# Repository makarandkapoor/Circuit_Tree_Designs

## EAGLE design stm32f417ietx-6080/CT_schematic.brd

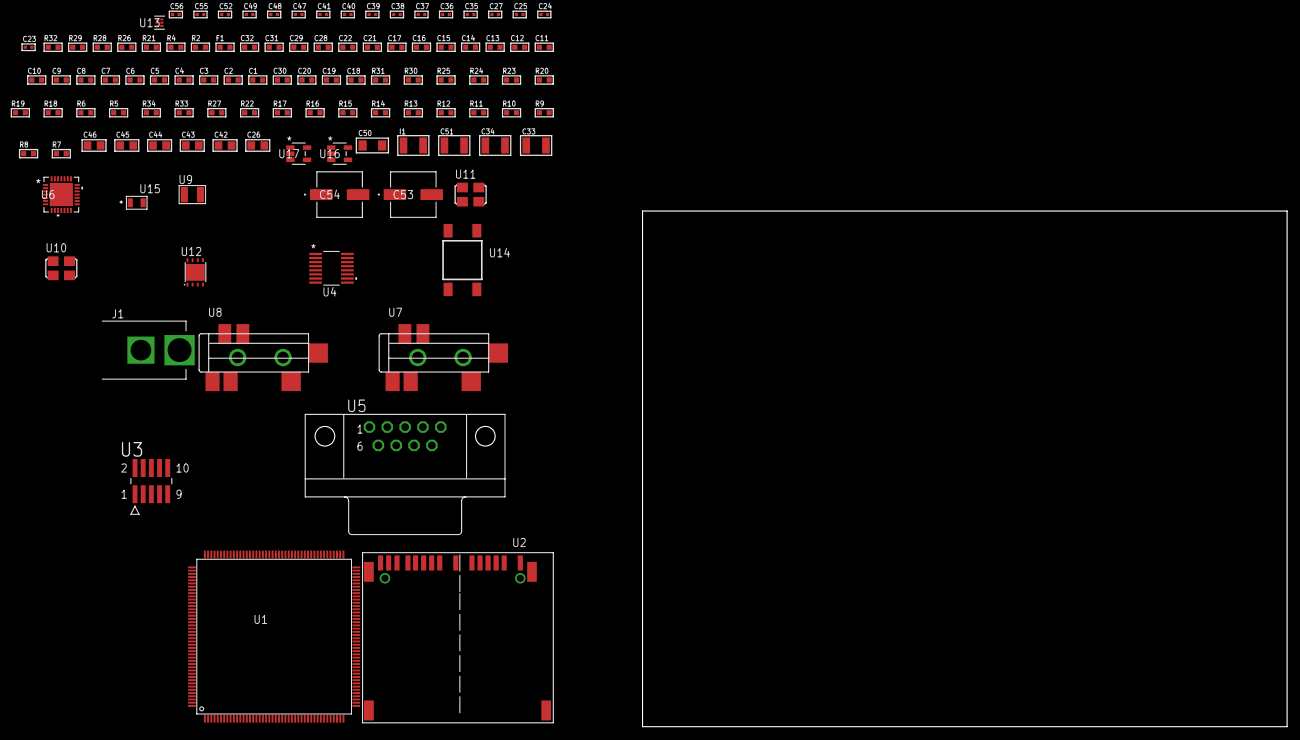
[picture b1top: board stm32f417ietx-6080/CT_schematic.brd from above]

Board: 2 copper layers, 100.0 x 80.0 mm, 108 parts (0 on the bottom side), 57 nets, no tracks yet.

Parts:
C1, C22, C28, C29, C31, C32: 1e-06; C0603
C2, C3, C4, C5, C6, C7, C8, C9, C10, C11, C12, C13, C14, C15, C16, C17: 1e-07; C0603
C18: 4.7e-06; C0603
C19, C20: 2.2e-06; C0603
C21: 1e-08; C0603
C23, C24: 1e-11; C0402
C25, C27, C37, C38, C39, C40, C41, C52: 1e-07; C0402
C26, C42, C43, C44, C45, C46: 1e-05; C0805
C30: 2.2e-07; C0603
C33, C34: 2.2e-05; C1210
C35, C36: 1e-09; C0402
C47, C48, C49, C55, C56: 1e-08; C0402
C50: 1e-05; C1206
C51: 1e-05; C1210
C53, C54: 0.0001; EXV-9H
F1: 240.0; L0603
I1: 1e-05; L1210
J1: PJ-037B; PJ-037B_PACKAGE
R2, R29: 1000.0; R0603
R4: 4700.0; R0603
R5, R6, R18, R19, R20, R30, R31: 10000.0; R0603
R7, R8, R9, R10, R11, R12, R13, R14, R15, R16, R17, R22, R27: 100000.0; R0603
R21: 5.0; R0603
R23, R24, R25: 47000.0; R0603
R26: 680.0; R0603
R28: 2231.0; R0603
R32: 9100.0; R0603
R33: 680000.0; R0603
R34: 120000.0; R0603
U1: STM32F417IET6; LQFP176
U2: 10100565
U3: FTSH-105-01-L-DV-K; SAMTEC_FTSH-105-01-L-DV-K
U4: LTC2804CGN-1#PBF; SSOP-16
U5: 182-009-113R531; 182-009-MALE
U6: WM8731CLSEFL; QFN-28
U7, U8: SJ-43515TS-SMT-TR
U9: ABS07-32.768KHZ-7-T
U10: ASFL1-12.288MHZ-EC-T; ASFL1
U11: ASFL1-25MHZ-NCS; ASFL1
U12: LP3878SDX-ADJ/NOPB; WSON-8
U13: TPS3895ADRYR; SON-6
U14: 4-1437565-2; SW_4-1437565-2
U15: Q65110A2395; LGM67K-G1J2-24-Z
U16, U17: nc7sz125m5x; NC7SZ125M5X

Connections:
CLK_CRYSTAL_U1_9: C23.1, U1.9, U9.1
CLK_CRYSTAL_U1_10: C24.1, U1.10, U9.2
CLK_U1_29: U1.29, U11.3
CLK_U6_1: U6.1, U10.3
GND: C1.2, C2.2, C3.2, C4.2, C5.2, C6.2, C7.2, C8.2, C9.2, C10.2, C11.2, C12.2, C13.2, C14.2, C15.2, C16.2, C17.2, C18.2, C19.2, C20.2, C21.2, C22.2, C23.2, C24.2, C25.2, C26.2, C27.2, C28.2, C29.2, C31.2, C32.2, C36.2, C37.2, C38.2, C39.2, C40.2, C41.2, C42.2, C43.2, C44.2, C45.2, C46.2, C47.2, C48.2, C49.2, C50.2, C51.2, C52.2, C53.2, C54.2, C55.2, C56.2, J1.2, R2.2, R6.2, R21.2, R23.2, R24.2, R25.2, R29.2, R32.2, R34.2, U1.14, U1.22, U1.37, U1.48, U1.61, U1.71, U1.90, U1.102, U1.113, U1.126, U1.135, U1.148, U1.158, U2.6, U2.10, U2.12, U2.16, U2.17, U2.20, U2.21, U3.3, U3.5, U4.8, U5.5, U6.4, U6.15, U6.19, U6.25, U6.26, U6.29, U7.1, U8.1, U10.2, U11.2, U12.3, U12.PAD, U13.2, U15.C, U16.2, U16.3, U17.1, U17.3
NET_U1_31: R4.1, U1.31, U17.4
NET_U1_39: C21.1, C22.1, F1.1, U1.38, U1.39
NET_U1_81: C19.1, U1.81
NET_U1_125: C20.1, U1.125
NET_U1_166: R6.1, U1.166
NET_U1_171: R5.1, U1.171
NET_U1_176: U14.3, U14.4
NET_U2_1: R9.1, U2.1
NET_U2_2: R8.1, U2.2
NET_U2_18: U2.18, U2.19
NET_U3_9: R21.1, U3.9
NET_U4_6: C28.1, U4.6
NET_U4_7: C30.1, I1.2, U4.7
NET_U4_9: C29.1, U4.9
NET_U4_10: C30.2, U4.10
NET_U4_11: R22.1, U4.11
NET_U5_2: U4.1, U5.2
NET_U5_3: U4.3, U5.3
NET_U5_7: U4.2, U5.7
NET_U5_8: U4.4, U5.8
NET_U6_20: C41.1, C46.1, U6.20
NET_U7_2: C34.1, R24.1, U7.2
NET_U7_5: C33.1, R23.1, U7.5
NET_U8_5: C35.1, C36.1, R25.1, R26.1, U8.5
NET_U12_1: C49.1, U12.1
NET_U12_6: R28.2, R29.1, U12.6
NET_U12_8: R27.1, U12.8
NET_U13_1: R31.1, R32.1, U13.1
NET_U13_3: R33.2, R34.1, U13.3
NET_U13_4: R30.1, U13.4, U16.4, U17.2
NET_U14_1: R2.1, U14.1, U14.2
PROC_I2S2_CK: U1.79, U6.7
PROC_I2S2_EXT_SD: U1.34, U6.10
PROC_I2S2_SD: U1.35, U6.8
PROC_I2S2_WS: U1.92, U6.9, U6.11
PROC_SDIO_CK: R7.1, U1.141, U2.8
PROC_SDIO_D0: R10.1, U1.117, U2.4
PROC_SDIO_D1: R11.1, U1.118, U2.3
PROC_SDIO_D2: R12.1, U1.139, U2.15
PROC_SDIO_D3: R13.1, U1.140, U2.14
PROC_SDIO_D4: R14.1, U1.167, U2.13
PROC_SDIO_D5: R15.1, U1.168, U2.11
PROC_SDIO_D6: R16.1, U1.115, U2.7
PROC_SDIO_D7: R17.1, U1.116, U2.5
PROC_SYS_JTCK_SWCLK: R19.1, U1.137, U3.4
PROC_SYS_JTDO_SWO: U1.161, U3.6
PROC_SYS_JTMS_SWDIO: R20.1, U1.124, U3.2
PROC_UART4_RX: U1.41, U4.16
PROC_UART4_TX: U1.40, U4.14
RST_OUT_U3_JTAG_RST_B: R18.1, U3.10, U16.1
VCC_S1_8V9: C50.1, C53.1, C54.1, J1.1, R27.2, U12.4
VCC_TIER1_3V3: C1.1, C2.1, C3.1, C4.1, C5.1, C6.1, C7.1, C8.1, C9.1, C10.1, C11.1, C12.1, C13.1, C14.1, C15.1, C16.1, C17.1, C18.1, C25.1, C26.1, C27.1, C31.1, C32.1, C37.1, C38.1, C39.1, C40.1, C42.1, C43.1, C44.1, C45.1, C47.1, C48.1, C51.1, C52.1, C55.1, C56.1, F1.2, I1.1, R4.2, R5.2, R7.2, R8.2, R9.2, R10.2, R11.2, R12.2, R13.2, R14.2, R15.2, R16.2, R17.2, R18.2, R19.2, R20.2, R22.2, R28.1, R30.2, R31.2, R33.1, U1.6, U1.15, U1.23, U1.36, U1.49, U1.62, U1.72, U1.82, U1.91, U1.103, U1.114, U1.127, U1.136, U1.149, U1.159, U1.172, U2.9, U3.1, U4.5, U4.12, U6.3, U6.5, U6.12, U6.18, U10.4, U11.4, U12.5, U13.6, U16.5, U17.5

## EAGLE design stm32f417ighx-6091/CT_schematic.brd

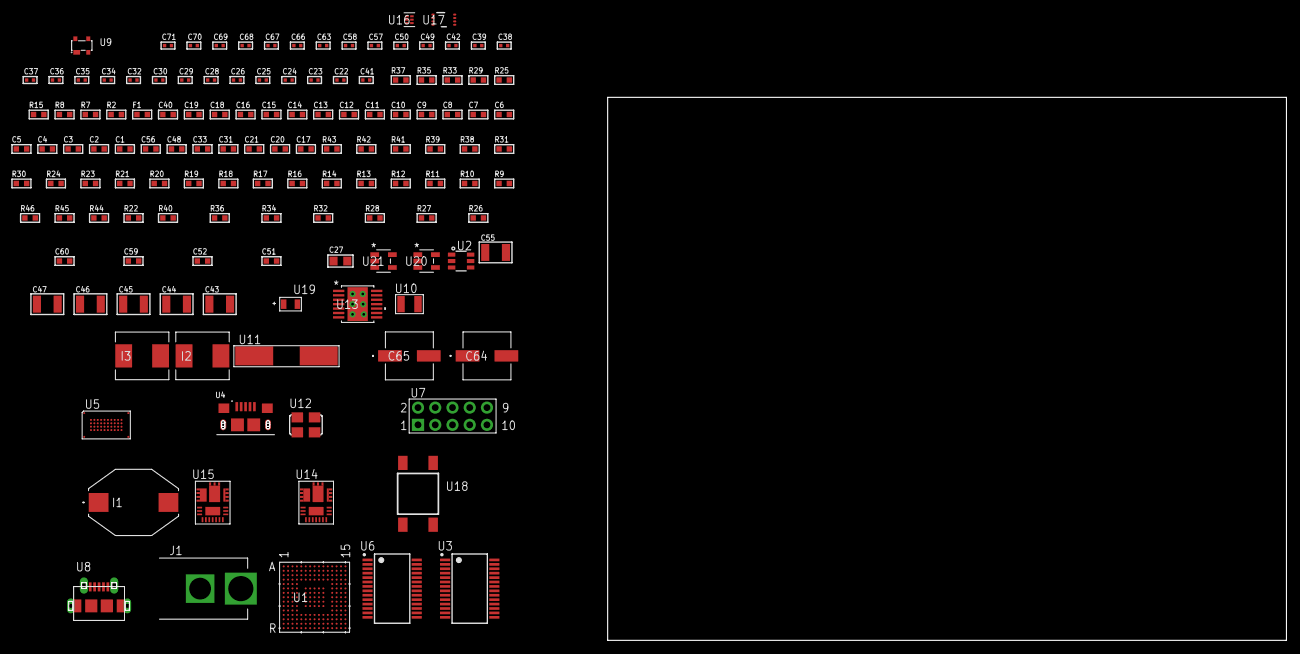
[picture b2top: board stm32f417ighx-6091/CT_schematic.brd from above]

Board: 2 copper layers, 134 parts (0 on the bottom side), 107 nets, no tracks yet.

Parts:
C1, C19, C40: 1e-06; C0603
C2, C3, C4, C5, C6, C7, C8, C9, C10, C11, C12, C13, C14, C15, C16: 1e-07; C0603
C17: 4.7e-06; C0603
C18: 1e-08; C0603
C20, C21, C31, C33, C48, C56: 2.2e-06; C0603
C22, C23, C24, C25: 1e-11; C0402
C26, C28, C29, C30, C32, C34, C35, C36, C37, C38, C42, C49, C50, C57, C58, C63, C67, C69: 1e-07; C0402
C27: 4.7e-06; C0805
C39, C66, C68, C70, C71: 1e-08; C0402
C41: 3.3e-09; C0402
C43, C44: 2.2e-05; C1210
C45, C46: 1e-05; C1210
C47, C55: 0.0001; C1210
C51, C59: 8.6971073877236e-09; R0603
C52, C60: 2.9649229730876e-07; R0603
C64, C65: 0.0001; EXV-9H
F1: 240.0; L0603
I1: 1e-05; IND_PM3316
I2, I3: 6.8e-07; IND25X25CZ
J1: PJ-037B; PJ-037B_PACKAGE
R2: 1000.0; R0603
R7, R8, R15: 4700.0; R0603
R9: 47000.0; R0603
R10, R11, R12, R13, R14, R16, R17, R18, R19, R20, R21, R41, R42: 10000.0; R0603
R22: 100000.0; R0603
R23: 30000.0; R0603
R24: 22000.0; R0603
R25, R33: 0.1; R0603
R26, R34: 4030.2416170974; R0603
R27: 719.68600305311; R0603
R28, R36: 58.613333333333; R0603
R29, R37: 130.0; R0603
R30, R38: 39000.0; R0603
R31, R39: 49900.0; R0603
R32, R40: 5147.5789473684; R0603
R35: 453.0; R0603
R43: 82000.0; R0603
R44: 300000.0; R0603
R45: 120000.0; R0603
R46: 200000.0; R0603
U1: STM32F417IGH6; UFBGA176_25
U2: MAX4995AAUT+T; SOT-23-6
U3: FT232RL-REEL; SSOP-28
U4: 10118193-0001LF; FCI_10118193-0001LF
U5: S29VS256RABBHW000
U6: ST3241EBPR; SSOP-28
U7: HTSS-105-01-G-D
U8: 47590-0001; MICRO_USB_AB
U9: prtr5v0u2ax; SOT143B
U10: ABS07-32.768KHZ-7-T
U11: ABLS-25.000MHZ-B2F-T
U12: ASFL1-12MHZ-NCS; ASFL1
U13: tps54225PWP; HTSSOP14
U14, U15: IR3899MTR1PBF
U16: TPS3895ADRYR; SON-6
U17: LSF0102DCTR; DCU0008A_N
U18: 4-1437565-2; SW_4-1437565-2
U19: Q65110A2395; LGM67K-G1J2-24-Z
U20, U21: nc7sz125m5x; NC7SZ125M5X

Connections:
CLK_CRYSTAL_U1_E1: C22.1, U1.E1, U10.1
CLK_CRYSTAL_U1_F1: C23.1, U1.F1, U10.2
CLK_CRYSTAL_U1_G1: C24.1, U1.G1, U11.1
CLK_CRYSTAL_U1_H1: C25.1, U1.H1, U11.2
CLK_U3_27: U3.27, U12.3
GND: C1.2, C2.2, C3.2, C4.2, C5.2, C6.2, C7.2, C8.2, C9.2, C10.2, C11.2, C12.2, C13.2, C14.2, C15.2, C16.2, C17.2, C18.2, C19.2, C20.2, C21.2, C22.2, C23.2, C24.2, C25.2, C26.2, C27.2, C28.2, C29.2, C30.2, C31.2, C32.2, C33.2, C34.2, C37.2, C38.2, C39.2, C40.2, C41.2, C43.2, C44.2, C45.2, C46.2, C48.2, C49.2, C50.2, C56.2, C57.2, C58.2, C63.2, C64.2, C65.2, C66.2, C67.2, C68.2, C69.2, C70.2, C71.2, J1.2, R2.2, R9.2, R11.2, R12.2, R14.2, R17.2, R24.2, R25.1, R25.2, R27.2, R30.2, R32.2, R33.1, R33.2, R35.2, R38.2, R40.2, R43.2, R45.2, U1.D5, U1.D7, U1.D8, U1.D9, U1.F2, U1.F6, U1.F7, U1.F8, U1.F9, U1.F10, U1.F12, U1.G2, U1.G6, U1.G7, U1.G8, U1.G9, U1.G10, U1.G12, U1.H6, U1.H7, U1.H8, U1.H9, U1.H10, U1.H12, U1.J6, U1.J7, U1.J8, U1.J9, U1.J10, U1.K6, U1.K7, U1.K8, U1.K9, U1.K10, U1.M1, U1.M8, U1.M9, U1.N1, U2.2, U3.7, U3.18, U3.21, U3.25, U3.26, U4.5, U4.6, U4.7, U4.8, U4.9, U5.C5, U5.D12, U5.E3, U5.F5, U6.23, U6.25, U7.9, U8.5, U8.6, U8.7, U8.8, U8.9, U9.1, U12.2, U13.5, U13.8, U13.9, U13.15, U14.4, U14.11, U14.17, U15.4, U15.11, U15.17, U16.2, U17.1, U19.C, U20.1, U20.3, U21.1, U21.3
NET_U1_C6: R10.1, U1.C6
NET_U1_D6: R11.1, U1.D6
NET_U1_F13: C21.1, U1.F13
NET_U1_J1: R8.1, U1.J1, U21.4
NET_U1_L4: R12.1, U1.L4
NET_U1_M10: C20.1, U1.M10
NET_U1_R1: C18.1, C19.1, F1.1, U1.P1, U1.R1
NET_U1_R15: U18.3, U18.4
NET_U2_3: R9.1, U2.3
NET_U3_14: R16.1, U3.14
NET_U3_17: C28.1, U3.17
NET_U3_19: R17.1, U3.19
NET_U4_1: R15.1, U4.1
NET_U4_2: U3.16, U4.2
NET_U4_3: U3.15, U4.3
NET_U5_D8: R7.1, U5.D8, U20.4
NET_U6_1: C36.1, U6.1
NET_U6_2: C36.2, U6.2
NET_U6_3: C38.1, U6.3
NET_U6_22: R22.1, U6.22
NET_U6_24: C35.2, U6.24
NET_U6_27: C37.1, U6.27
NET_U6_28: C35.1, U6.28
NET_U7_3: U6.4, U7.3
NET_U7_4: U6.5, U7.4
NET_U7_5: U6.9, U7.5
NET_U7_6: U6.10, U7.6
NET_U13_2: R23.2, R24.1, U13.2
NET_U13_3: C40.1, U13.3
NET_U13_4: C41.1, U13.4
NET_U13_10: C42.1, I1.1, U13.10, U13.11
NET_U13_12: C42.2, U13.12
NET_U14_1: C51.1, R26.1, R27.1, R28.1, R29.1, U14.1, U14.8
NET_U14_2: C50.1, U14.2
NET_U14_3: C51.2, C52.1, C52.2, U14.3
NET_U14_5: R30.1, U14.5
NET_U14_10: C48.1, U14.10
NET_U14_12: C47.1, I2.1, U14.12
NET_U14_14: C47.2, U14.14
NET_U14_15: R31.1, R32.1, U14.15
NET_U14_ATNET_3: I2.2, R26.2
NET_U14_ATNET_4: C52.2, R28.2
NET_U15_1: C59.1, R34.1, R35.1, R36.1, R37.1, U15.1, U15.8
NET_U15_2: C58.1, U15.2
NET_U15_3: C59.2, C60.1, C60.2, U15.3
NET_U15_5: R38.1, U15.5
NET_U15_10: C56.1, U15.10
NET_U15_12: C55.1, I3.1, U15.12
NET_U15_14: C55.2, U15.14
NET_U15_15: R39.1, R40.1, U15.15
NET_U15_ATNET_3: I3.2, R34.2
NET_U15_ATNET_4: C60.2, R36.2
NET_U16_1: R42.1, R43.1, U16.1
NET_U16_3: R44.2, R45.1, U16.3
NET_U16_4: R41.1, U16.4, U20.2, U21.2
NET_U17_8: R46.1, U17.8
NET_U18_1: R2.1, U18.1, U18.2
PROC_FSMC_A16: U1.N14, U5.D4
PROC_FSMC_A17: U1.N13, U5.C11
PROC_FSMC_A18: U1.M15, U5.D10
PROC_FSMC_A19: U1.A1, U5.C10
PROC_FSMC_A20: U1.B1, U5.D5
PROC_FSMC_A21: U1.B2, U5.C4
PROC_FSMC_A22: U1.B3, U5.C12
PROC_FSMC_A23: U1.A2, U5.D7
PROC_FSMC_CLK: U1.D11, U5.C6
PROC_FSMC_D0: U1.M14, U5.F3
PROC_FSMC_D1: U1.L14, U5.F4
PROC_FSMC_D2: U1.B12, U5.E6
PROC_FSMC_D3: U1.C12, U5.E7
PROC_FSMC_D4: U1.R8, U5.F8
PROC_FSMC_D5: U1.P8, U5.F9
PROC_FSMC_D6: U1.P9, U5.E10
PROC_FSMC_D7: U1.R9, U5.E11
PROC_FSMC_D8: U1.P10, U5.E4
PROC_FSMC_D9: U1.R10, U5.E5
PROC_FSMC_D10: U1.N11, U5.F6
PROC_FSMC_D11: U1.P11, U5.F7
PROC_FSMC_D12: U1.R11, U5.E8
PROC_FSMC_D13: U1.P15, U5.E9
PROC_FSMC_D14: U1.P14, U5.F11
PROC_FSMC_D15: U1.N15, U5.F12
PROC_FSMC_NE4: R19.1, U1.B8, U5.D11
PROC_FSMC_NL: U1.B5, U5.D6
PROC_FSMC_NOE: R21.1, U1.D10, U5.E12
PROC_FSMC_NWAIT: R18.1, U1.B11, U5.C3
PROC_FSMC_NWE: R20.1, U1.C11, U5.C8
PROC_GPIO_TO_U1_USB_FAULT: R13.1, U1.A4, U2.6
PROC_GPIO_TO_U1_VBUS_EN: R14.1, U1.A3, U2.4
PROC_UART4_RX_TOXCVR: U6.19, U17.6
PROC_UART4_TX_TOXCVR: U6.14, U17.5
PROC_UART5_RX: U1.D12, U3.1
PROC_UART5_TX: U1.A12, U3.5
PROC_USB_OTG_FS_DM: U1.C15, U8.2, U9.3
PROC_USB_OTG_FS_DP: U1.B15, U8.3, U9.2
PROC_USB_OTG_FS_ID: U1.D15, U8.4
PROC_USB_OTG_FS_VBUS: U1.E15, U2.1, U8.1, U9.4
VCC_S1_16V8: C45.1, C46.1, C49.1, C57.1, C64.1, C65.1, J1.1, R31.2, R39.2, U13.7, U13.13, U13.14, U14.9, U15.9
VCC_TIER1_1V8: C1.1, C2.1, C3.1, C4.1, C5.1, C6.1, C7.1, C8.1, C9.1, C10.1, C11.1, C12.1, C13.1, C14.1, C15.1, C16.1, C17.1, C29.1, C30.1, C31.1, C32.1, C33.1, C43.1, C44.1, C63.1, C68.1, C69.1, C70.1, C71.1, F1.2, I1.2, R7.2, R8.2, R10.2, R13.2, R18.2, R19.2, R20.2, R21.2, R23.1, R41.2, R42.2, R44.1, U1.C1, U1.C5, U1.C7, U1.C8, U1.C9, U1.F3, U1.G3, U1.G13, U1.H13, U1.J12, U1.J13, U1.K4, U1.N8, U1.N9, U1.N10, U3.4, U5.C7, U5.D3, U5.F10, U13.1, U16.6, U17.2, U20.5, U21.5
VCC_TIER1_3V3: C26.1, C27.1, C34.1, C39.1, C66.1, C67.1, I2.2, R16.2, R22.2, R26.2, R46.2, U3.20, U6.26, U12.4, U17.7
VCC_TIER1_5V0: I3.2, R34.2, U2.5

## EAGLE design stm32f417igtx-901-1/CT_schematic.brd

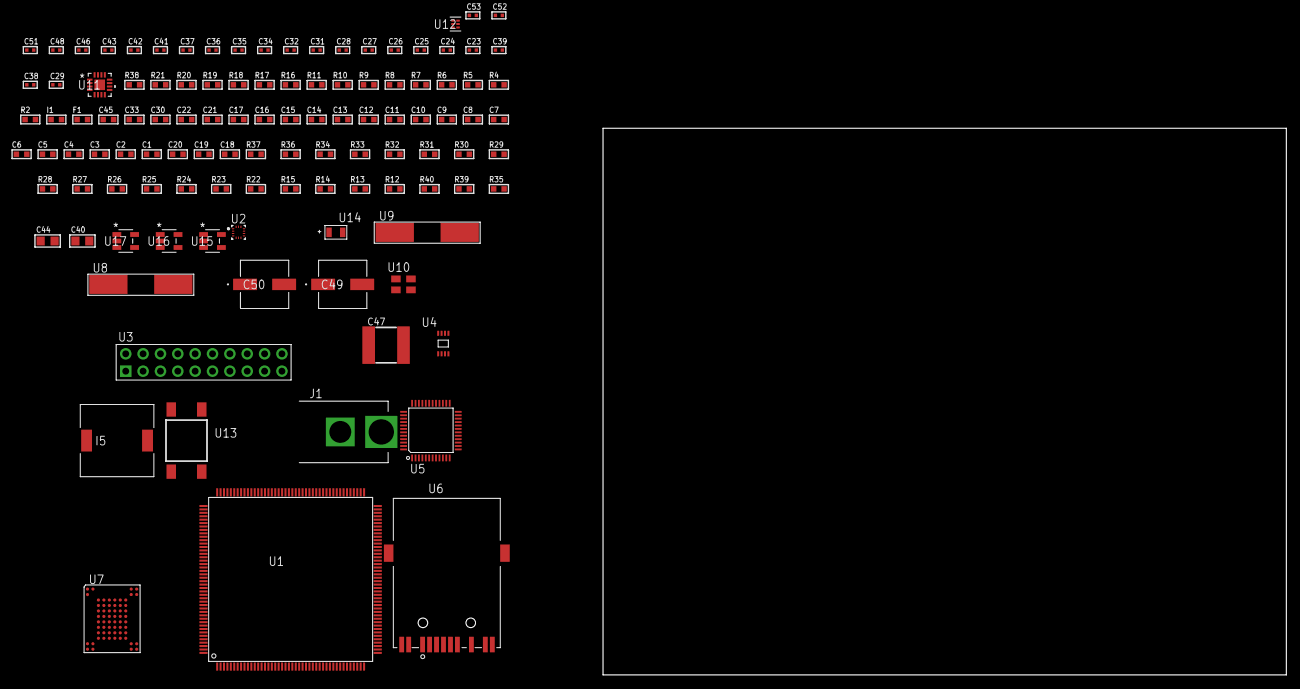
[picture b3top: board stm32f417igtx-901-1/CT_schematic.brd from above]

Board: 2 copper layers, 100.0 x 80.0 mm, 112 parts (0 on the bottom side), 83 nets, no tracks yet.

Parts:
C1, C22, C30, C33, C45: 1e-06; C0603
C2, C3, C4, C5, C6, C7, C8, C9, C10, C11, C12, C13, C14, C15, C16, C17: 1e-07; C0603
C18: 4.7e-06; C0603
C19, C20: 2.2e-06; C0603
C21: 1e-08; C0603
C23, C24: 1e-11; C0402
C25, C26, C27, C31, C34, C36, C37, C41, C42, C46, C48: 1e-07; C0402
C28, C32, C35, C43, C51, C52, C53: 1e-08; C0402
C29: 2.2e-08; C0402
C38, C39: 2.7e-11; C0402
C40, C44: 1e-05; C0805
C47: 6.8e-05; 2220
C49, C50: 0.0001; EXV-9H
F1: 240.0; L0603
I1: 97.0; R0603
I5: 3.8e-06; DR1040
J1: PJ-037B; PJ-037B_PACKAGE
R2: 1000.0; R0603
R4, R5, R21: 4700.0; R0603
R6, R7, R8, R9, R10, R11: 2200.0; R0603
R12, R13, R14, R15, R22, R23, R24, R25, R26, R27, R28, R29, R30, R31, R32, R36, R37: 10000.0; R0603
R16, R17: 0.1; R0603
R18, R19: 200.0; R0603
R20: 2490.0; R0603
R33: 20000.0; R0603
R34: 91000.0; R0603
R35: 300000.0; R0603
R38: 9100.0; R0603
R39: 680000.0; R0603
R40: 120000.0; R0603
U1: STM32F417IGT6; LQFP176
U2: BMC150; LGA14R35P5X6_200X200X100
U3: TST-110-05-T-D-RA
U4: 24AA02T-I/MNY; TDFN-8/6MM
U5: RTL8201FL-VB-CG
U6: 7498011122R
U7: TH58NVG3S0HBAI4
U8, U9: ABLS-25.000MHZ-B2F-T
U10: ASEK-32.768KHz-ECST; ASEK
U11: LTC3601EUD#PBF; QFN-16_EP
U12: TPS3895ADRYR; SON-6
U13: 4-1437565-2; SW_4-1437565-2
U14: Q65110A2395; LGM67K-G1J2-24-Z
U15, U16, U17: nc7sz125m5x; NC7SZ125M5X

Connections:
CLK_CRYSTAL_U1_29: C23.1, U1.29, U8.1
CLK_CRYSTAL_U1_30: C24.1, U1.30, U8.2
CLK_CRYSTAL_U5_42: C39.1, U5.42, U9.1
CLK_CRYSTAL_U5_43: C38.1, U5.43, U9.2
CLK_U1_9: U1.9, U10.3
GND: C1.2, C2.2, C3.2, C4.2, C5.2, C6.2, C7.2, C8.2, C9.2, C10.2, C11.2, C12.2, C13.2, C14.2, C15.2, C16.2, C17.2, C18.2, C19.2, C20.2, C21.2, C22.2, C23.2, C24.2, C25.2, C26.2, C27.2, C28.2, C29.2, C30.2, C31.2, C32.2, C33.2, C34.2, C35.2, C36.2, C37.2, C38.2, C39.2, C40.2, C41.2, C42.2, C43.2, C44.2, C45.2, C47.1, C47.2, C48.2, C49.2, C50.2, C51.2, C52.2, C53.2, J1.2, R2.2, R13.2, R16.2, R17.2, R20.2, R22.2, R24.2, R25.2, R26.2, R33.2, R35.2, R38.2, R40.2, U1.14, U1.22, U1.37, U1.48, U1.61, U1.71, U1.90, U1.102, U1.113, U1.126, U1.135, U1.148, U1.158, U2.1, U2.6, U2.7, U2.9, U3.4, U3.6, U3.8, U3.10, U3.12, U3.14, U3.16, U3.18, U3.20, U4.4, U5.7, U5.20, U5.33, U5.47, U6.11, U7.C5, U7.K3, U7.K8, U10.2, U11.1, U11.9, U11.17, U12.2, U14.C, U15.2, U15.3, U16.1, U16.3, U17.1, U17.3
NET_U1_16: R9.1, U1.16, U4.5
NET_U1_17: R8.1, U1.17, U4.6
NET_U1_31: R5.1, U1.31, U17.4
NET_U1_33: R10.1, U1.33, U5.30
NET_U1_39: C21.1, C22.1, F1.1, U1.38, U1.39
NET_U1_42: R11.1, U1.42, U5.31
NET_U1_81: C19.1, U1.81
NET_U1_125: C20.1, U1.125
NET_U1_164: R6.1, U1.164, U2.11
NET_U1_165: R7.1, U1.165, U2.14
NET_U1_166: R13.1, U1.166
NET_U1_171: R12.1, U1.171
NET_U1_176: U13.3, U13.4
NET_U5_6: C30.1, C31.1, C32.1, I1.1, U5.6, U5.41
NET_U5_10: R25.1, U5.10
NET_U5_29: R4.1, U5.29, U16.4
NET_U5_32: R21.1, U5.32
NET_U5_34: R23.1, U5.34
NET_U5_35: R24.1, U5.35
NET_U5_40: C37.1, U5.40
NET_U5_46: R20.1, U5.46
NET_U5_48: C36.1, U5.48
NET_U6_1: U5.1, U6.1
NET_U6_3: U5.2, U6.3
NET_U6_4: U5.4, U6.4
NET_U6_5: C29.1, U6.2, U6.5
NET_U6_6: U5.5, U6.6
NET_U6_8: R17.1, U6.8
NET_U6_10: R18.1, U6.10
NET_U6_12: R19.1, U6.12
NET_U6_13: R16.1, U6.13, U6.14
NET_U7_C3: R31.1, U7.C3
NET_U11_3: C46.2, I5.1, U11.3, U11.4
NET_U11_6: C46.1, U11.6
NET_U11_7: C45.1, U11.7, U11.12
NET_U11_10: R35.1, U11.10
NET_U11_11: R33.1, R34.1, U11.11
NET_U11_ATNET_3: I5.2, R34.2
NET_U12_1: R37.1, R38.1, U12.1
NET_U12_3: R39.2, R40.1, U12.3
NET_U12_4: R36.1, U12.4, U15.4, U16.2, U17.2
NET_U13_1: R2.1, U13.1, U13.2
PROC_ETH_COL: U1.44, U5.38
PROC_ETH_CRS: U1.40, U5.36
PROC_ETH_RXD0: U1.54, U5.14
PROC_ETH_RXD1: U1.55, U5.16
PROC_ETH_RXD2: U1.56, U5.17
PROC_ETH_RXD3: R26.1, U1.57, U5.18
PROC_ETH_RX_CLK: U1.41, U5.19
PROC_ETH_RX_DV: R22.1, U1.53, U5.13
PROC_ETH_RX_ER: R27.1, U1.12, U5.39
PROC_ETH_TXD0: U1.92, U5.23
PROC_ETH_TXD1: U1.93, U5.24
PROC_ETH_TXD2: U1.34, U5.25
PROC_ETH_TXD3: U1.1, U5.26
PROC_ETH_TX_CLK: U1.35, U5.22
PROC_ETH_TX_EN: U1.80, U5.27
PROC_FSMC_A16: U1.99, U7.D5
PROC_FSMC_A17: U1.100, U7.C4
PROC_FSMC_D0: U1.104, U7.H4
PROC_FSMC_D1: U1.105, U7.J4
PROC_FSMC_D2: U1.142, U7.K4
PROC_FSMC_D3: U1.143, U7.K5
PROC_FSMC_D4: U1.68, U7.K6
PROC_FSMC_D5: U1.69, U7.J7
PROC_FSMC_D6: U1.70, U7.K7
PROC_FSMC_D7: U1.73, U7.J8
PROC_FSMC_INT2: R32.1, U1.110, U7.C8
PROC_FSMC_NCE2: R28.1, U1.151, U7.C6
PROC_FSMC_NOE: R29.1, U1.146, U7.D4
PROC_FSMC_NWE: R30.1, U1.147, U7.C7
PROC_SYS_JTCK_SWCLK: U1.137, U3.9
PROC_SYS_JTDO_SWO: U1.161, U3.13
PROC_SYS_JTMS_SWDIO: U1.124, U3.7
RST_OUT_U3_SRESET_B: R15.1, U3.15, U15.1
VCC_S1_13V5: C44.1, C49.1, C50.1, J1.1, U11.15, U11.16
VCC_TIER1_3V3: C1.1, C2.1, C3.1, C4.1, C5.1, C6.1, C7.1, C8.1, C9.1, C10.1, C11.1, C12.1, C13.1, C14.1, C15.1, C16.1, C17.1, C18.1, C25.1, C26.1, C27.1, C28.1, C33.1, C34.1, C35.1, C40.1, C41.1, C42.1, C43.1, C47.2, C48.1, C51.1, C52.1, C53.1, F1.2, I1.2, I5.2, R4.2, R5.2, R6.2, R7.2, R8.2, R9.2, R10.2, R11.2, R12.2, R14.1, R14.2, R15.2, R21.2, R23.2, R27.2, R28.2, R29.2, R30.2, R31.2, R32.2, R34.2, R36.2, R37.2, R39.1, U1.6, U1.15, U1.23, U1.36, U1.49, U1.62, U1.72, U1.82, U1.91, U1.103, U1.114, U1.127, U1.136, U1.149, U1.159, U1.172, U2.8, U2.10, U2.12, U2.13, U3.1, U4.7, U4.8, U5.15, U5.21, U5.37, U7.H8, U7.J6, U10.4, U11.8, U12.6, U15.5, U16.5, U17.5

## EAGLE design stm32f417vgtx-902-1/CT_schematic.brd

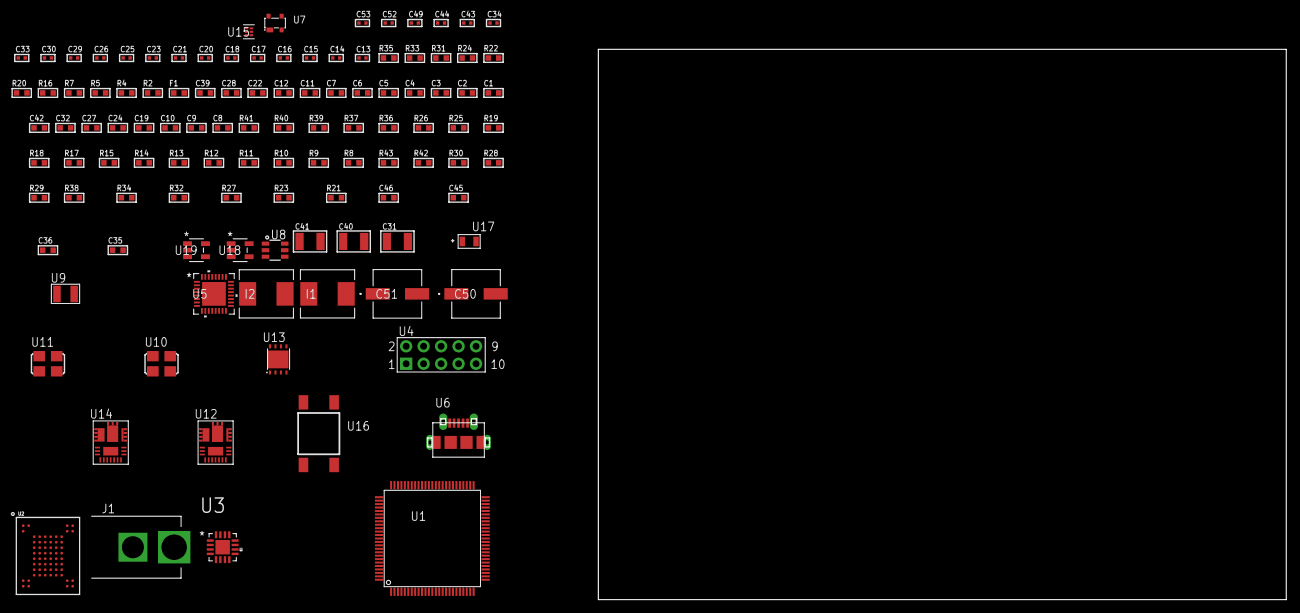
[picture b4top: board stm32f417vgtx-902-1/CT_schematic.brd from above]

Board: 2 copper layers, 124.8 x 80.0 mm, 112 parts (0 on the bottom side), 86 nets, no tracks yet.

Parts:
C1, C12, C22, C28: 1e-06; C0603
C2, C3, C4, C5, C6, C7: 1e-07; C0603
C8: 4.7e-06; C0603
C9, C10, C19, C24, C27, C32, C42: 2.2e-06; C0603
C11: 1e-08; C0603
C13, C14: 1e-11; C0402
C15, C16, C17, C18, C20, C21, C23, C25, C26, C33, C34, C43, C44, C49: 1e-07; C0402
C29, C30, C52, C53: 1e-08; C0402
C31, C41: 0.0001; C1210
C35, C45: 8.6971073877236e-09; R0603
C36, C46: 2.9649229730876e-07; R0603
C39: 8e-07; R0603
C40: 1e-05; C1210
C50, C51: 0.0001; EXV-9H
F1: 240.0; L0603
I1, I2: 6.8e-07; IND25X25CZ
J1: PJ-037B; PJ-037B_PACKAGE
R2: 1000.0; R0603
R4, R5: 4700.0; R0603
R7: 2200.0; R0603
R8, R9, R10, R11, R12, R13, R14, R15, R18, R19, R39, R40: 10000.0; R0603
R16: 47.0; R0603
R17: 47000.0; R0603
R20, R31: 0.1; R0603
R21, R32: 4030.2416170974; R0603
R22: 1600.0; R0603
R23, R34: 58.613333333333; R0603
R24, R35: 130.0; R0603
R25, R36: 39000.0; R0603
R26, R37: 49900.0; R0603
R27, R38: 5147.5789473684; R0603
R28, R30: 100000.0; R0603
R29: 153694.38; R0603
R33: 453.0; R0603
R41: 82000.0; R0603
R42: 300000.0; R0603
R43: 120000.0; R0603
U1: STM32F417VGT6; LQFP100
U2: mt29f4g08abbdah4; VFBGA-63
U3: TSC2013QRSARQ1; QFN65P400X400X100-17N
U4: HTSS-105-01-G-D
U5: TUSB1210BRHBR; RHB32_3P45X3P45
U6: 47590-0001; MICRO_USB_AB
U7: prtr5v0u2ax; SOT143B
U8: MAX4995AAUT+T; SOT-23-6
U9: ABS07-32.768KHZ-7-T
U10: ASFL1-25MHZ-NCS; ASFL1
U11: ASFL1-26MHZ-NCS; ASFL1
U12, U14: IR3899MTR1PBF
U13: LP2951ACSDX/NOPB; WSON-8
U15: TPS3895ADRYR; SON-6
U16: 4-1437565-2; SW_4-1437565-2
U17: Q65110A2395; LGM67K-G1J2-24-Z
U18, U19: nc7sz125m5x; NC7SZ125M5X

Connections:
CLK_CRYSTAL_U1_8: C13.1, U1.8, U9.1
CLK_CRYSTAL_U1_9: C14.1, U1.9, U9.2
CLK_U1_12: U1.12, U10.3
CLK_U5_1: U5.1, U11.3
GND: C1.2, C2.2, C3.2, C4.2, C5.2, C6.2, C7.2, C8.2, C9.2, C10.2, C11.2, C12.2, C13.2, C14.2, C15.2, C16.2, C17.2, C18.2, C19.2, C23.2, C24.2, C25.2, C26.2, C27.2, C28.2, C29.2, C30.2, C32.2, C33.2, C34.2, C39.2, C40.2, C42.2, C43.2, C44.2, C49.2, C50.2, C51.2, C52.2, C53.2, J1.2, R2.2, R8.2, R17.2, R20.1, R20.2, R22.2, R25.2, R27.2, R30.2, R31.1, R31.2, R33.2, R36.2, R38.2, R41.2, R43.2, U1.10, U1.20, U1.27, U1.74, U1.99, U2.C5, U2.F7, U2.K3, U2.K8, U3.17, U4.9, U5.33, U6.5, U6.6, U6.7, U6.8, U6.9, U7.1, U8.2, U10.2, U11.2, U12.4, U12.11, U12.17, U13.3, U13.4, U13.PAD, U14.4, U14.11, U14.17, U15.2, U17.C, U18.1, U18.3, U19.1, U19.3
NET_U1_14: R4.1, U1.14, U18.4
NET_U1_22: C11.1, C12.1, F1.1, U1.21, U1.22
NET_U1_49: C9.1, U1.49
NET_U1_73: C10.1, U1.73
NET_U1_93: R7.1, U1.93, U3.1
NET_U1_94: R8.1, U1.94
NET_U1_98: U16.3, U16.4
NET_U2_C3: R13.1, U2.C3
NET_U3_4: R15.1, U3.4
NET_U3_5: R14.1, U3.5
NET_U3_9: C20.2, C21.2, C22.2, R16.2, U3.9
NET_U3_15: R16.1, U3.8, U3.15
NET_U4_3: U3.12, U4.3
NET_U4_4: U3.14, U4.4
NET_U4_5: U3.11, U4.5
NET_U4_6: U3.13, U4.6
NET_U5_11: R18.1, U5.11
NET_U5_12: C27.1, U5.12
NET_U5_14: R19.1, U5.14
NET_U5_20: C24.1, U5.20
NET_U5_27: R5.1, U5.27, U19.4
NET_U6_1: C28.1, U5.22, U6.1, U7.4, U8.1
NET_U6_2: U5.19, U6.2, U7.3
NET_U6_3: U5.18, U6.3, U7.2
NET_U6_4: U5.23, U6.4
NET_U8_3: R17.1, U8.3
NET_U8_4: U5.17, U8.4
NET_U12_1: C35.1, R21.1, R22.1, R23.1, R24.1, U12.1, U12.8
NET_U12_2: C34.1, U12.2
NET_U12_3: C35.2, C36.1, C36.2, U12.3
NET_U12_5: R25.1, U12.5
NET_U12_10: C32.1, U12.10
NET_U12_12: C31.1, I1.1, U12.12
NET_U12_14: C31.2, U12.14
NET_U12_15: R26.1, R27.1, U12.15
NET_U12_ATNET_3: I1.2, R21.2
NET_U12_ATNET_4: C36.2, R23.2
NET_U13_5: R28.1, U13.5
NET_U13_7: R29.2, R30.1, U13.7
NET_U14_1: C45.1, R32.1, R33.1, R34.1, R35.1, U14.1, U14.8
NET_U14_2: C44.1, U14.2
NET_U14_3: C45.2, C46.1, C46.2, U14.3
NET_U14_5: R36.1, U14.5
NET_U14_10: C42.1, U14.10
NET_U14_12: C41.1, I2.1, U14.12
NET_U14_14: C41.2, U14.14
NET_U14_15: R37.1, R38.1, U14.15
NET_U14_ATNET_3: I2.2, R32.2
NET_U14_ATNET_4: C46.2, R34.2
NET_U15_1: R40.1, R41.1, U15.1
NET_U15_3: R42.2, R43.1, U15.3
NET_U15_4: R39.1, U15.4, U18.2, U19.2
NET_U16_1: R2.1, U16.1, U16.2
PROC_FSMC_D0: U1.61, U2.H4
PROC_FSMC_D1: U1.62, U2.J4
PROC_FSMC_D2: U1.81, U2.K4
PROC_FSMC_D3: U1.82, U2.K5
PROC_FSMC_D4: U1.38, U2.K6
PROC_FSMC_D5: U1.39, U2.J7
PROC_FSMC_D6: U1.40, U2.K7
PROC_FSMC_D7: U1.41, U2.J8
PROC_FSMC_NCE2: R10.1, U1.88, U2.C6
PROC_FSMC_NOE: R12.1, U1.85, U2.D4
PROC_FSMC_NWAIT: R9.1, U1.87, U2.C8
PROC_FSMC_NWE: R11.1, U1.86, U2.C7
PROC_USB_OTG_HS_ULPI_CK: U1.30, U5.26
PROC_USB_OTG_HS_ULPI_D0: U1.26, U5.3
PROC_USB_OTG_HS_ULPI_D1: U1.35, U5.4
PROC_USB_OTG_HS_ULPI_D2: U1.36, U5.5
PROC_USB_OTG_HS_ULPI_D3: U1.47, U5.6
PROC_USB_OTG_HS_ULPI_D4: U1.48, U5.7
PROC_USB_OTG_HS_ULPI_D5: U1.51, U5.9
PROC_USB_OTG_HS_ULPI_D6: U1.52, U5.10
PROC_USB_OTG_HS_ULPI_D7: U1.91, U5.13
PROC_USB_OTG_HS_ULPI_DIR: U1.17, U5.31
PROC_USB_OTG_HS_ULPI_NXT: U1.18, U5.2
PROC_USB_OTG_HS_ULPI_STP: U1.15, U5.29
VCC_S1_16V8: C33.1, C39.1, C43.1, C50.1, C51.1, J1.1, R26.2, R37.2, U12.9, U13.8, U14.9
VCC_TIER1_1V8: C1.1, C2.1, C3.1, C4.1, C5.1, C6.1, C7.1, C8.1, C15.1, C16.1, C17.1, C18.1, C19.1, C20.1, C25.1, C26.1, C49.1, C52.1, C53.1, F1.2, I1.2, R4.2, R5.2, R7.2, R9.2, R10.2, R11.2, R12.2, R13.2, R14.2, R15.2, R18.2, R19.2, R21.2, R39.2, R40.2, R42.1, U1.6, U1.11, U1.19, U1.28, U1.50, U1.75, U1.100, U2.D3, U2.G4, U2.H8, U2.J6, U3.7, U5.28, U5.30, U5.32, U15.6, U18.5, U19.5
VCC_TIER1_3V3: C21.1, C22.1, C23.1, C29.1, C30.1, C40.1, R28.2, R29.1, U3.10, U5.21, U10.4, U11.4, U13.1
VCC_TIER1_5V0: I2.2, R32.2, U8.5

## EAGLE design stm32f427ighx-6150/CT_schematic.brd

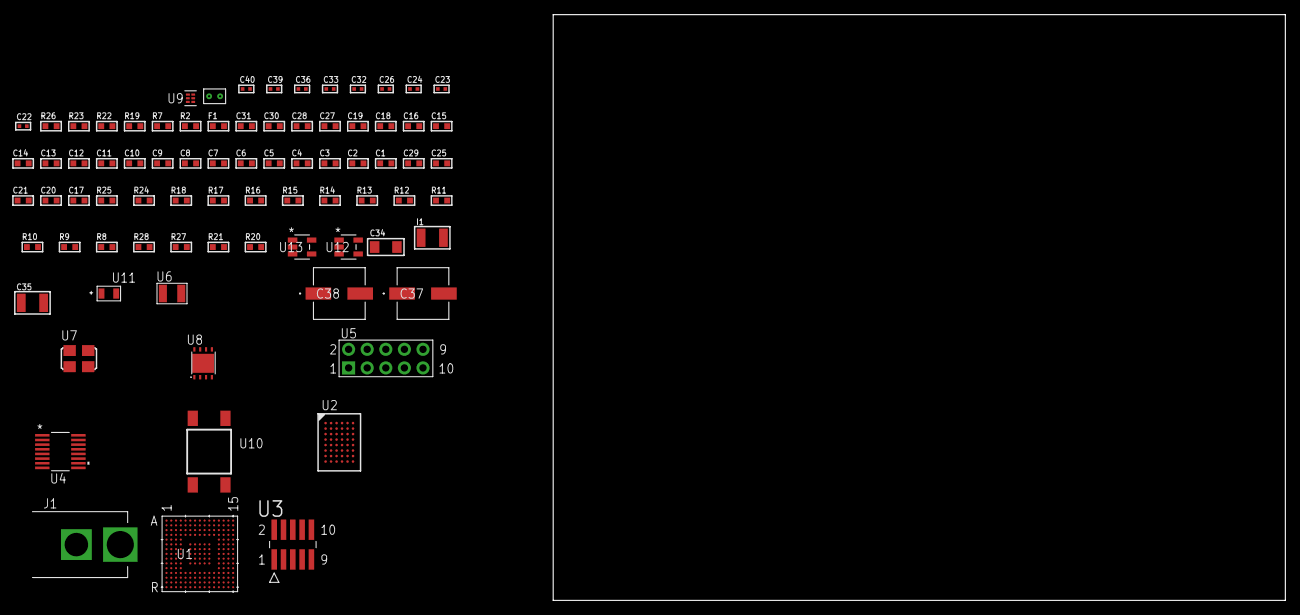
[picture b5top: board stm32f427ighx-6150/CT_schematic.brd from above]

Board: 2 copper layers, 100.0 x 80.0 mm, 80 parts (0 on the bottom side), 78 nets, no tracks yet.

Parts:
C1, C19, C27, C28, C30, C31: 1e-06; C0603
C2, C3, C4, C5, C6, C7, C8, C9, C10, C11, C12, C13, C14, C15, C16: 1e-07; C0603
C17: 4.7e-06; C0603
C18: 1e-08; C0603
C20, C21, C25: 2.2e-06; C0603
C22, C23: 1e-11; C0402
C24, C26, C36: 1e-07; C0402
C29: 2.2e-07; C0603
C32, C33, C39, C40: 1e-08; C0402
C34: 1e-05; C1206
C35: 1e-05; C1210
C37, C38: 0.0001; EXV-9H
F1: 240.0; L0603
I1: 1e-05; L1210
J1: PJ-037B; PJ-037B_PACKAGE
R2, R23: 1000.0; R0603
R7: 4700.0; R0603
R8, R9, R10, R11, R12, R13, R14, R15, R16, R17, R18, R24, R25: 10000.0; R0603
R19: 5.0; R0603
R20, R21: 100000.0; R0603
R22: 2231.0; R0603
R26: 9100.0; R0603
R27: 680000.0; R0603
R28: 120000.0; R0603
U1: STM32F427IGH6; UFBGA176_25
U2: CY62147GE30-45BVXI; VFBGA48
U3: FTSH-105-01-L-DV-K; SAMTEC_FTSH-105-01-L-DV-K
U4: LTC2804CGN-1#PBF; SSOP-16
U5: HTSS-105-01-G-D
U6: ABS07-32.768KHZ-7-T
U7: ASFL1-25MHZ-NCS; ASFL1
U8: LP3878SDX-ADJ/NOPB; WSON-8
U9: TPS3895ADRYR; SON-6
U10: 4-1437565-2; SW_4-1437565-2
U11: Q65110A2395; LGM67K-G1J2-24-Z
U12, U13: nc7sz125m5x; NC7SZ125M5X
U14: Dummy; DUMMY_PACKAGE_168

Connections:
CLK_CRYSTAL_U1_E1: C22.1, U1.E1, U6.1
CLK_CRYSTAL_U1_F1: C23.1, U1.F1, U6.2
CLK_U1_G1: U1.G1, U7.3
GND: C1.2, C2.2, C3.2, C4.2, C5.2, C6.2, C7.2, C8.2, C9.2, C10.2, C11.2, C12.2, C13.2, C14.2, C15.2, C16.2, C17.2, C18.2, C19.2, C20.2, C21.2, C22.2, C23.2, C24.2, C25.2, C26.2, C27.2, C28.2, C30.2, C31.2, C32.2, C33.2, C34.2, C35.2, C36.2, C37.2, C38.2, C39.2, C40.2, J1.2, R2.2, R10.2, R11.2, R18.2, R19.2, R23.2, R26.2, R28.2, U1.D5, U1.D7, U1.D8, U1.D9, U1.F2, U1.F6, U1.F7, U1.F8, U1.F9, U1.F10, U1.F12, U1.G2, U1.G6, U1.G7, U1.G8, U1.G9, U1.G10, U1.G12, U1.H6, U1.H7, U1.H8, U1.H9, U1.H10, U1.H12, U1.J6, U1.J7, U1.J8, U1.J9, U1.J10, U1.K6, U1.K7, U1.K8, U1.K9, U1.K10, U1.M1, U1.M8, U1.M9, U1.N1, U2.D1, U2.E6, U3.3, U3.5, U4.8, U5.9, U7.2, U8.3, U8.PAD, U9.2, U11.C, U12.2, U12.3, U13.1, U13.3, U14.1
NET_U1_C6: R8.1, U1.C6
NET_U1_D6: R9.1, U1.D6
NET_U1_F13: C21.1, U1.F13
NET_U1_J1: R7.1, U1.J1, U13.4
NET_U1_L4: R11.1, U1.L4
NET_U1_M6: R10.1, U1.M6
NET_U1_M10: C20.1, U1.M10
NET_U1_R1: C18.1, C19.1, F1.1, U1.P1, U1.R1
NET_U1_R15: U10.3, U10.4
NET_U3_9: R19.1, U3.9
NET_U4_6: C27.1, U4.6
NET_U4_7: C29.1, I1.2, U4.7
NET_U4_9: C28.1, U4.9
NET_U4_10: C29.2, U4.10
NET_U4_11: R20.1, U4.11
NET_U5_3: U4.1, U5.3
NET_U5_4: U4.2, U5.4
NET_U5_5: U4.3, U5.5
NET_U5_6: U4.4, U5.6
NET_U8_1: C33.1, U8.1
NET_U8_6: R22.2, R23.1, U8.6
NET_U8_8: R21.1, U8.8
NET_U9_1: R25.1, R26.1, U9.1
NET_U9_3: R27.2, R28.1, U9.3
NET_U9_4: R24.1, U9.4, U12.4, U13.2
NET_U10_1: R2.1, U10.1, U10.2
PROC_DAC_OUT2: U1.P4, U14.2
PROC_FMC_A0: U1.E2, U2.A3
PROC_FMC_A1: U1.H3, U2.A4
PROC_FMC_A2: U1.H2, U2.A5
PROC_FMC_A3: U1.J2, U2.B3
PROC_FMC_A4: U1.J3, U2.B4
PROC_FMC_A5: U1.K3, U2.C3
PROC_FMC_A6: U1.P6, U2.C4
PROC_FMC_A7: U1.N6, U2.D4
PROC_FMC_A8: U1.R7, U2.H2
PROC_FMC_A9: U1.P7, U2.H3
PROC_FMC_A10: U1.N7, U2.H4
PROC_FMC_A11: U1.M7, U2.H5
PROC_FMC_A12: U1.L15, U2.G3
PROC_FMC_A13: U1.K15, U2.G4
PROC_FMC_A14: U1.K14, U2.F3
PROC_FMC_A15: U1.K13, U2.F4
PROC_FMC_A16: U1.N14, U2.E4
PROC_FMC_A17: U1.N13, U2.D3
PROC_FMC_D0: U1.M14, U2.B6
PROC_FMC_D1: U1.L14, U2.C5
PROC_FMC_D2: U1.B12, U2.C6
PROC_FMC_D3: U1.C12, U2.D5
PROC_FMC_D4: U1.R8, U2.E5
PROC_FMC_D5: U1.P8, U2.F5
PROC_FMC_D6: U1.P9, U2.F6
PROC_FMC_D7: U1.R9, U2.G6
PROC_FMC_D8: U1.P10, U2.B1
PROC_FMC_D9: U1.R10, U2.C1
PROC_FMC_D10: U1.N11, U2.C2
PROC_FMC_D11: U1.P11, U2.D2
PROC_FMC_D12: U1.R11, U2.E2
PROC_FMC_D13: U1.P15, U2.F2
PROC_FMC_D14: U1.P14, U2.F1
PROC_FMC_D15: U1.N15, U2.G1
PROC_FMC_NBL0: U1.A4, U2.A1
PROC_FMC_NE2: R13.1, U1.C10, U2.B5
PROC_FMC_NOE: R12.1, U1.D10, U2.A2
PROC_FMC_NWE: R14.1, U1.C11, U2.G5
PROC_SYS_JTCK_SWCLK: R18.1, U1.A14, U3.4
PROC_SYS_JTDI: R16.1, U1.A13, U3.8
PROC_SYS_JTDO_SWO: U1.A10, U3.6
PROC_SYS_JTMS_SWDIO: R17.1, U1.A15, U3.2
PROC_UART4_RX: U1.B13, U4.16
PROC_UART4_TX: U1.B14, U4.14
RST_OUT_U3_JTAG_RST_B: R15.1, U3.10, U12.1
VCC_S1_8V1: C34.1, C37.1, C38.1, J1.1, R21.2, U8.4
VCC_TIER1_3V3: C1.1, C2.1, C3.1, C4.1, C5.1, C6.1, C7.1, C8.1, C9.1, C10.1, C11.1, C12.1, C13.1, C14.1, C15.1, C16.1, C17.1, C24.1, C25.1, C26.1, C30.1, C31.1, C32.1, C35.1, C36.1, C39.1, C40.1, F1.2, I1.1, R7.2, R8.2, R9.2, R12.2, R13.2, R14.2, R15.2, R16.2, R17.2, R20.2, R22.1, R24.2, R25.2, R27.1, U1.C1, U1.C5, U1.C7, U1.C8, U1.C9, U1.F3, U1.G3, U1.G13, U1.H13, U1.J12, U1.J13, U1.K4, U1.N8, U1.N9, U1.N10, U2.D6, U2.E1, U3.1, U4.5, U4.12, U7.4, U8.5, U9.6, U12.5, U13.5
